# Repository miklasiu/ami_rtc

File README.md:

# ami_rtc
 Amiga 500 RTC module using EPSON RTC62421A chip.

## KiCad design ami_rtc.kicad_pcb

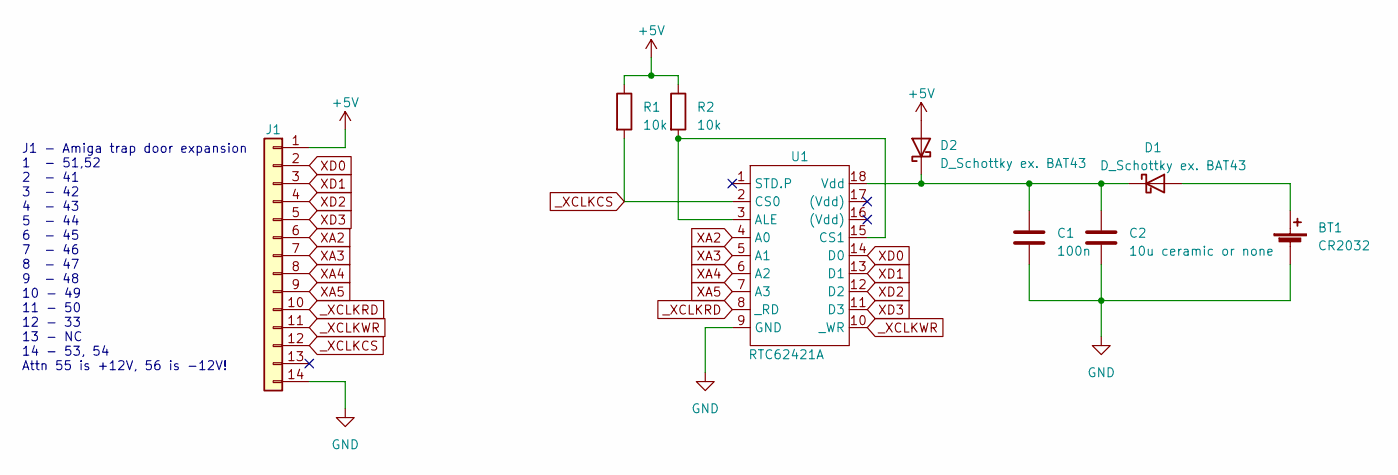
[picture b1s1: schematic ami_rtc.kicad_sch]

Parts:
BT1: CR2032; BatteryHolder_Keystone_103_1x20mm
C1: 100n; C_1206_3216Metric_Pad1.33x1.80mm_HandSolder
C2: 10u ceramic or none; C_1812_4532Metric_Pad1.57x3.40mm_HandSolder
D1, D2: D_Schottky ex. BAT43; D_DO-35_SOD27_P7.62mm_Horizontal
J1: Conn_01x14; PinHeader_1x14_P2.54mm_Vertical
R1, R2: 10k; R_1206_3216Metric_Pad1.30x1.75mm_HandSolder
U1: RTC62421A; DIP-18_W7.62mm_LongPads

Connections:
+5V: D2.2 (A), J1.1, R1.1, R2.1
GND: BT1.2 (-), C1.2, C2.2, J1.14, U1.9 (GND)
unnamed: BT1.1 (+), D1.2 (A)
unnamed: C1.1, C2.1, D1.1 (K), D2.1 (K), U1.18 (Vdd)
unnamed: R2.2, U1.3 (ALE), U1.15 (CS1)
XA2: J1.6, U1.4 (A0)
XA3: J1.7, U1.5 (A1)
XA4: J1.8, U1.6 (A2)
XA5: J1.9, U1.7 (A3)
XD0: J1.2, U1.14 (D0)
XD1: J1.3, U1.13 (D1)
XD2: J1.4, U1.12 (D2)
XD3: J1.5, U1.11 (D3)
_XCLKCS: J1.12, R1.2, U1.2 (CS0)
_XCLKRD: J1.10, U1.8 (_RD)
_XCLKWR: J1.11, U1.10 (_WR)

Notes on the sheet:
J1 - Amiga trap door expansion 1 - 51,52 2 - 41 3 - 42 4 - 43 5 - 44 6 - 45 7 - 46 8 - 47 9 - 48 10 - 49 11 - 50 12 - 33 13 - NC 14 - 53, 54 Attn 55 is +12V, 56 is -12V!

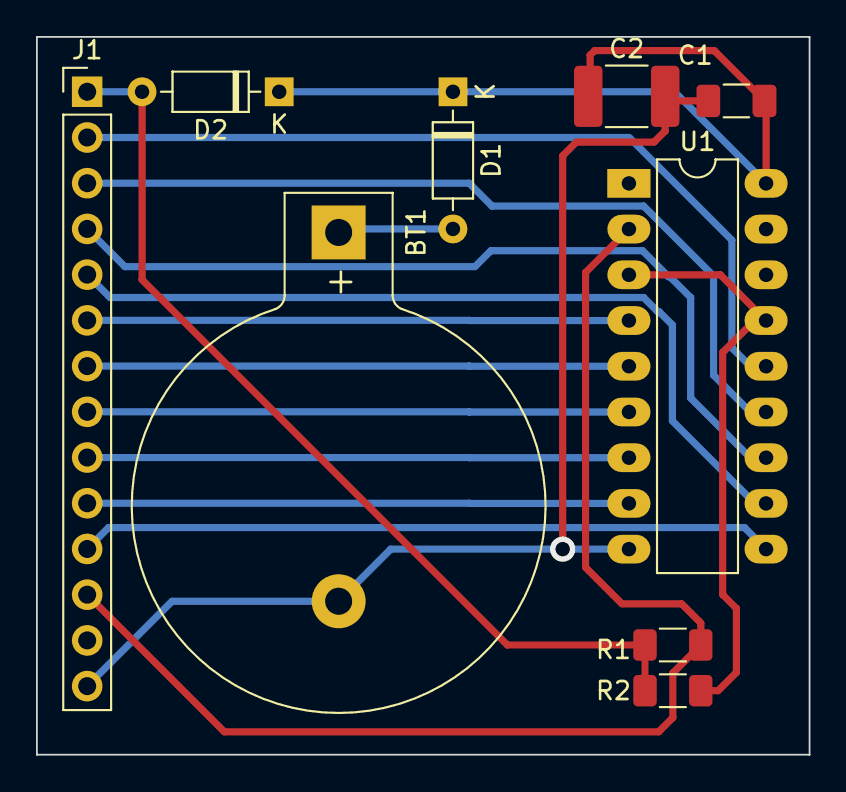
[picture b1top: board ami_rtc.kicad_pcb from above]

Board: 2 copper layers, 42.9 x 39.9 mm, 9 parts (0 on the bottom side), 16 nets.

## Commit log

2024-01-06 It works! ;)
2024-01-06 Ignore kicad backups
2024-01-06 some photos
